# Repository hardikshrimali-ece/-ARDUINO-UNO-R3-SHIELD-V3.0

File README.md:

# -ARDUINO-UNO-R3-SHIELD-V3.0
Arduino Uno Multifunction Shield V3.0 built in KiCad with integrated 4-digit MAX7219 display, UART, I2C, PWM, power headers, buzzer, LEDs, and push buttons. Optimized for embedded systems learning, testing, and rapid hardware prototyping.

Overview

The Arduino Uno Multifunction Development Shield V3.0 is an improved version of my previous V2.0 shield, designed to make Arduino prototyping, embedded learning, and peripheral testing faster and more organized.

Unlike many commercial multifunction shields, this version focuses on accessibility, usability, and future expandability while maintaining compatibility with the Arduino Uno.

---

Objectives

- Simplify Arduino development
- Reduce external wiring
- Provide dedicated communication interfaces
- Improve board usability
- Create a reusable development platform
- https://github.com/hardikshrimali-ece/CUSTOM-ARDUINO-UNO-R3-SHILED-V2.0.git    refer this for code and function

---

Features

- 4-Digit 7-Segment Display (MAX7219 Driver)
- Five User Push Buttons
- Piezo Buzzer
- Power Status LED
- UART Status LEDs (TX/RX)
- Dedicated UART Header
- Dedicated I2C Header
- Dedicated PWM Header
- Dedicated Power Header (VIN, 3.3V, 5V, GND)
- Arduino Uno Shield Compatibility

---

Improvements over V2.0

1. Improved Display Placement

The display has been repositioned to improve mechanical balance and make the shield visually cleaner.

Benefit

- Better weight distribution
- Improved accessibility
- Cleaner PCB layout

---

2. Dedicated UART Connector

A dedicated UART breakout has been added.

Pins:

- RX
- TX
- 5V
- GND

Benefit

- Easy connection of:
  - ESP32
  - Bluetooth Modules
  - GPS
  - Serial Debugging Devices

---

3. Dedicated I2C Connector

Added a dedicated I2C interface.

Pins:

- SDA
- SCL
- 5V
- GND

Benefit

Quick connection for:

- OLED Displays
- IMU Sensors
- RTC Modules
- EEPROM
- Environmental Sensors

---

4. Dedicated PWM Header

Multiple PWM pins are grouped together.

Benefit

Easy testing of:

- Servo Motors
- ESCs
- PWM Controlled Devices

---

5. Dedicated Power Distribution

Separate power breakout:

- VIN
- 3.3V
- 5V
- GND

Benefit

Reduces jumper wiring during prototyping.

---

6. Better Silkscreen Labels

Every interface is clearly labeled.

Examples:

- UART
- I2C
- PWM
- Power
- TX
- RX
- VIN
- 5V
- GND

Benefit

Improves usability and reduces wiring mistakes.

---

Design Philosophy

Rather than simply copying an existing multifunction shield, this project redesigns the layout with emphasis on:

- Better user experience
- Organized headers
- Easier debugging
- Better expandability
- Improved accessibility

---

Applications

- Embedded Systems Learning
- Arduino Programming
- Sensor Testing
- UART Experiments
- I2C Communication
- PWM Experiments
- Educational Labs
- Rapid Prototyping

---

Current Status

- Schematic Completed
- PCB Designed
- DRC Completed
- Through-hole Prototype Planned
- Hardware Testing Pending

---

Future Work

- Through-hole prototype validation
- Functional testing
- PCB manufactured version
- V4.0 with additional peripherals
- Arduino Nano version
- ESP32 version

---

Designed by: Hardik Shrimali

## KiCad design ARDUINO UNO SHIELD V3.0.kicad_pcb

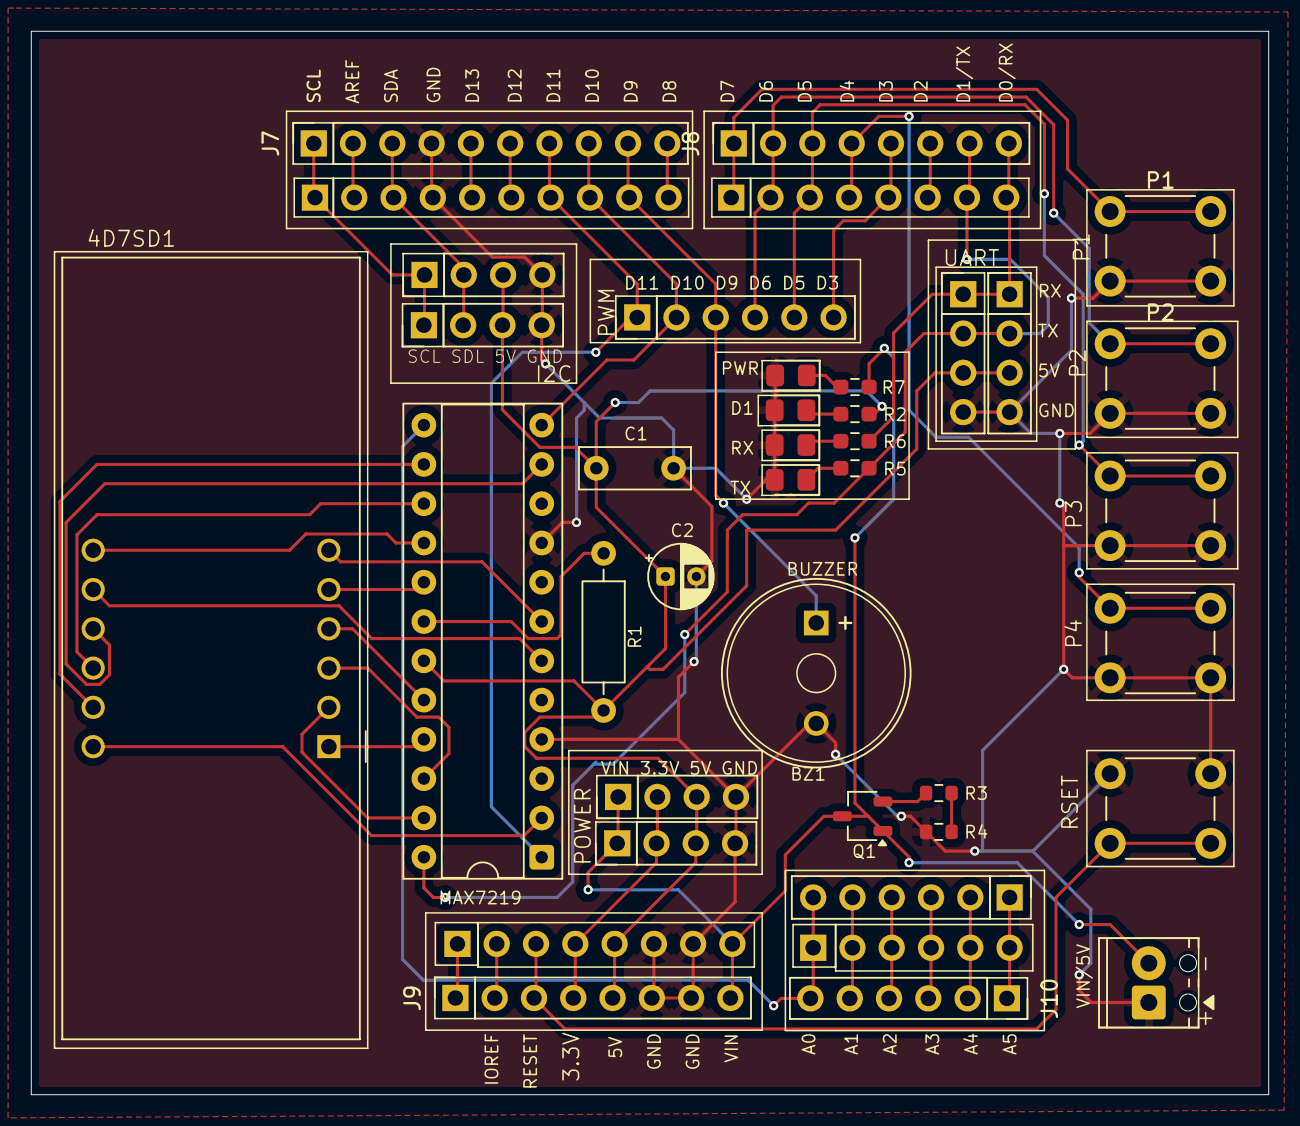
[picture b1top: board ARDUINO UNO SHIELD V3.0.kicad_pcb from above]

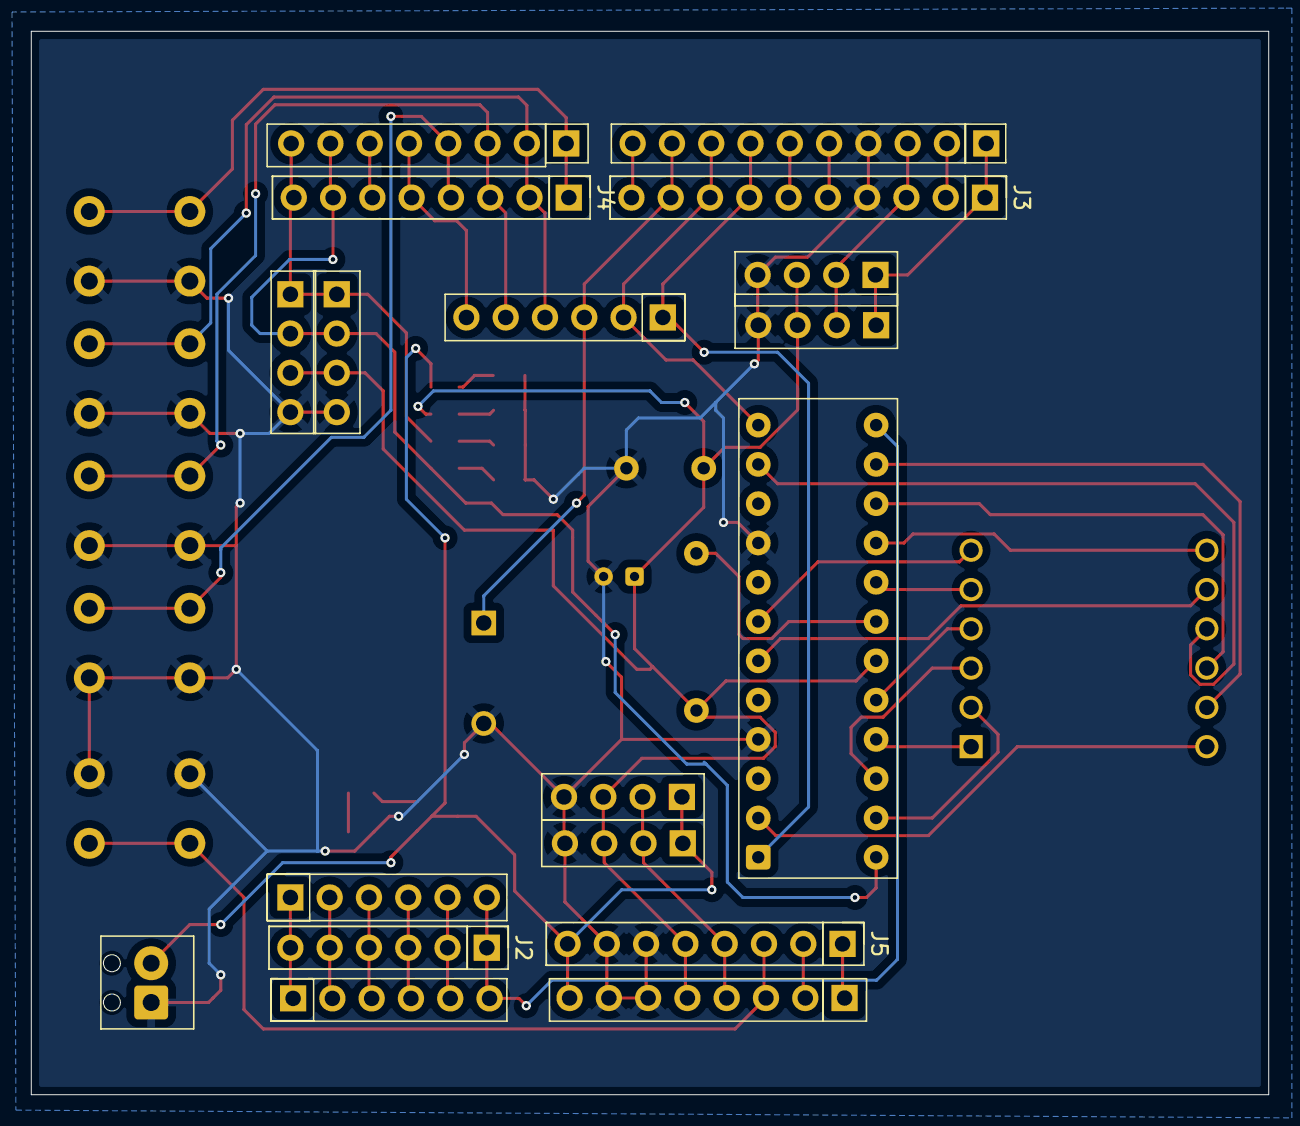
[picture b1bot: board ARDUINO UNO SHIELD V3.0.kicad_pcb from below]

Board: 2 copper layers, 80.0 x 68.8 mm, 39 parts (4 on the bottom side), 49 nets.

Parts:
4D7SD1: CC56-12EWA; CA56-12EWA
BZ1: Buzzer; MagneticBuzzer_ProSignal_ABT-410-RC
C1: 0.1mF; C_Disc_D7.0mm_W2.5mm_P5.00mm
C2: 10mF; CP_Radial_D4.0mm_P2.00mm
D1: LED; LED_0805_2012Metric_Pad1.15x1.40mm_HandSolder
I2C1, I2C2: I2C; PinHeader_1x04_P2.54mm_Vertical
J1: VIN 5V; TerminalBlock_Phoenix_MPT-0,5-2-2.54_1x02_P2.54mm_Horizontal
J2: ANALOG; PinHeader_1x06_P2.54mm_Vertical
J3: digital01; PinHeader_1x10_P2.54mm_Vertical
J4: digital02; PinHeader_1x08_P2.54mm_Vertical
J5: ANALOG01; PinHeader_1x08_P2.54mm_Vertical
J6: analog02; PinHeader_1x06_P2.54mm_Vertical
J7: digital01d; PinSocket_1x10_P2.54mm_Vertical
J8: digital02D; PinSocket_1x08_P2.54mm_Vertical
J9: ANALOG01D; PinSocket_1x08_P2.54mm_Vertical
J10: analog02; PinSocket_1x06_P2.54mm_Vertical
P1, P2, P3, P4: SW_Push; SW_PUSH_6mm_H5mm
PWR1, PWR2: I2C; PinHeader_1x04_P2.54mm_Vertical
Q1: PMOS_Substrate; TSOT-23
R1: 10k; R_Axial_DIN0207_L6.3mm_D2.5mm_P10.16mm_Horizontal
R2, R5, R6, R7: 1.2k; R_0603_1608Metric_Pad0.98x0.95mm_HandSolder
R3: 100k; R_0603_1608Metric
R4: 100; R_0603_1608Metric
RSET1: SW_Push; SW_PUSH_6mm_H5mm
SPIN1: PWM; PinHeader_1x06_P2.54mm_Vertical
U1: MAX7219; DIP-24_W7.62mm_Socket
UART1, UART2: I2C; PinHeader_1x04_P2.54mm_Vertical
pwrd1: LED; LED_0805_2012Metric_Pad1.15x1.40mm_HandSolder
rxd1: LED; LED_0805_2012Metric_Pad1.15x1.40mm_HandSolder
txd1: LED; LED_0805_2012Metric_Pad1.15x1.40mm_HandSolder

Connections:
3.3V: J5.4, J9.4, PWR1.2, PWR2.2
5V: C1.1, C2.1, I2C1.3, I2C2.3, J5.5, J9.5, PWR1.3, PWR2.3, R1.2, R2.2, U1.19 (V+), UART1.3, UART2.3
A0: J2.6, J6.1, J10.1
A1: J2.5, J6.2, J10.2
A2: J2.4, J6.3, J10.3
A3: J2.3, J6.4, J10.4
A4: J2.2, J6.5, J10.5
A5: J2.1, J6.6, J10.6, U1.13 (CLK)
D2: J4.6, J8.6
D3: J4.5, J8.5, SPIN1.6
D4: J4.4, J8.4, P4.1
D5: J4.3, J8.3, P3.1, SPIN1.5
D6: J4.2, J8.2, P2.1, SPIN1.4
D7: J4.1, J8.1, P1.1
D8: J3.10, J7.10
D9: BZ1.1 (+), J3.9, J7.9, SPIN1.3
D10: J3.8, J7.8, SPIN1.2, U1.12 (LOAD)
D11: J3.7, J7.7, SPIN1.1, U1.1 (DIN)
D12: J3.6, J7.6
D13: J3.5, J7.5
GND: BZ1.2 (-), C1.2, C2.2, D1.2 (A), I2C1.4, I2C2.4, J1.1, J3.4, J5.6, J5.7, J7.4, J9.6, J9.7, P1.2, P2.2, P3.2, P4.2, PWR1.4, PWR2.4, R4.1, RSET1.1, U1.4 (GND), U1.9 (GND), UART1.4, UART2.4, pwrd1.2 (A), rxd1.2 (A), txd1.2 (A)
unnamed: 4D7SD1.12 (CC1), U1.2 (DIG_0)
unnamed: 4D7SD1.9 (CC2), U1.11 (DIG_1)
unnamed: 4D7SD1.8 (CC3), U1.6 (DIG_2)
unnamed: 4D7SD1.6 (CC4), U1.7 (DIG_3)
unnamed: 4D7SD1.3 (DPX), U1.22 (SEG_DP)
unnamed: 4D7SD1.11 (a), U1.14 (SEG_A)
unnamed: 4D7SD1.7 (b), U1.16 (SEG_B)
unnamed: 4D7SD1.4 (c), U1.20 (SEG_C)
unnamed: 4D7SD1.2 (d), U1.23 (SEG_D)
unnamed: 4D7SD1.1 (e), U1.21 (SEG_E)
unnamed: 4D7SD1.10 (f), U1.15 (SEG_F)
unnamed: 4D7SD1.5 (g), U1.17 (SEG_G)
unnamed: D1.1 (K), R2.1
unnamed: J3.2, J7.2
unnamed: J5.1, J9.1
unnamed: J5.2, J9.2
unnamed: J5.3, J9.3, RSET1.2
unnamed: Q1.2 (G), R3.2
unnamed: R3.1, R4.2
unnamed: R1.1, U1.18 (ISET)
unnamed: R7.1, pwrd1.1 (K)
unnamed: R6.1, rxd1.1 (K)
unnamed: R5.1, txd1.1 (K)
RX: J4.8, J8.8, R6.2, UART1.1, UART2.1
SCL: I2C1.1, I2C2.1, J3.1, J7.1
SDA: I2C1.2, I2C2.2, J3.3, J7.3
TX: J4.7, J8.7, R5.2, U1.24 (DOUT), UART1.2, UART2.2
VIN: J1.2, J5.8, J9.8, PWR1.1, PWR2.1, Q1.1 (D), Q1.3 (S), R7.2
